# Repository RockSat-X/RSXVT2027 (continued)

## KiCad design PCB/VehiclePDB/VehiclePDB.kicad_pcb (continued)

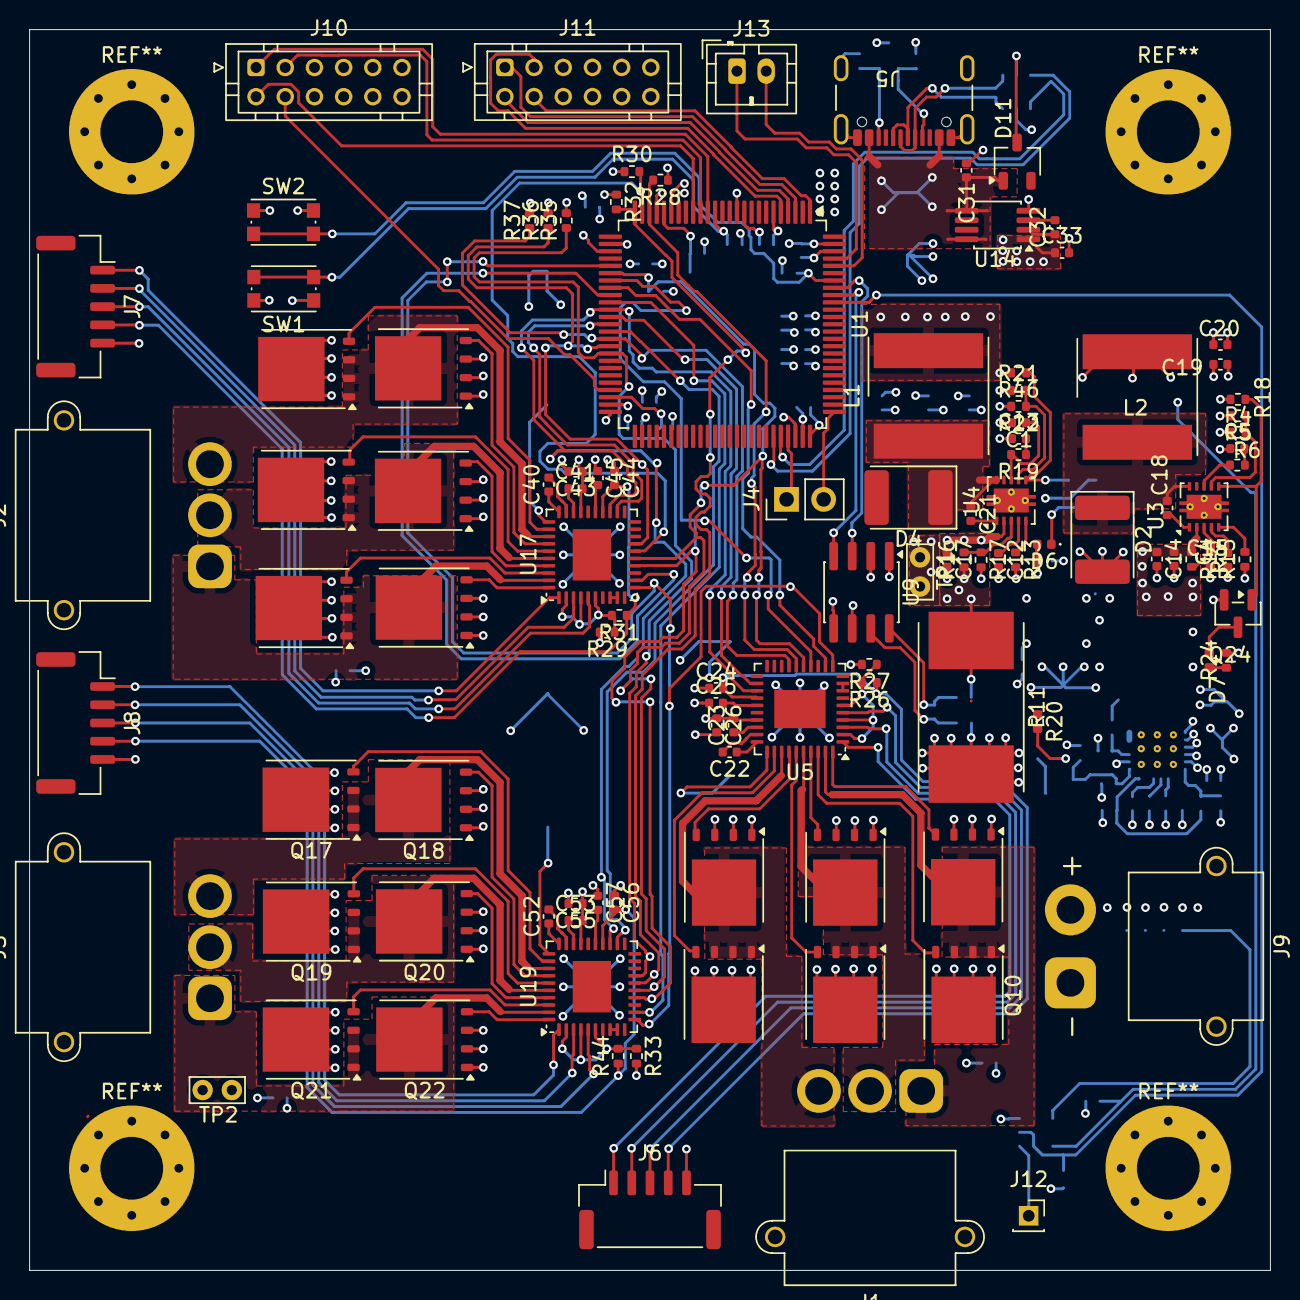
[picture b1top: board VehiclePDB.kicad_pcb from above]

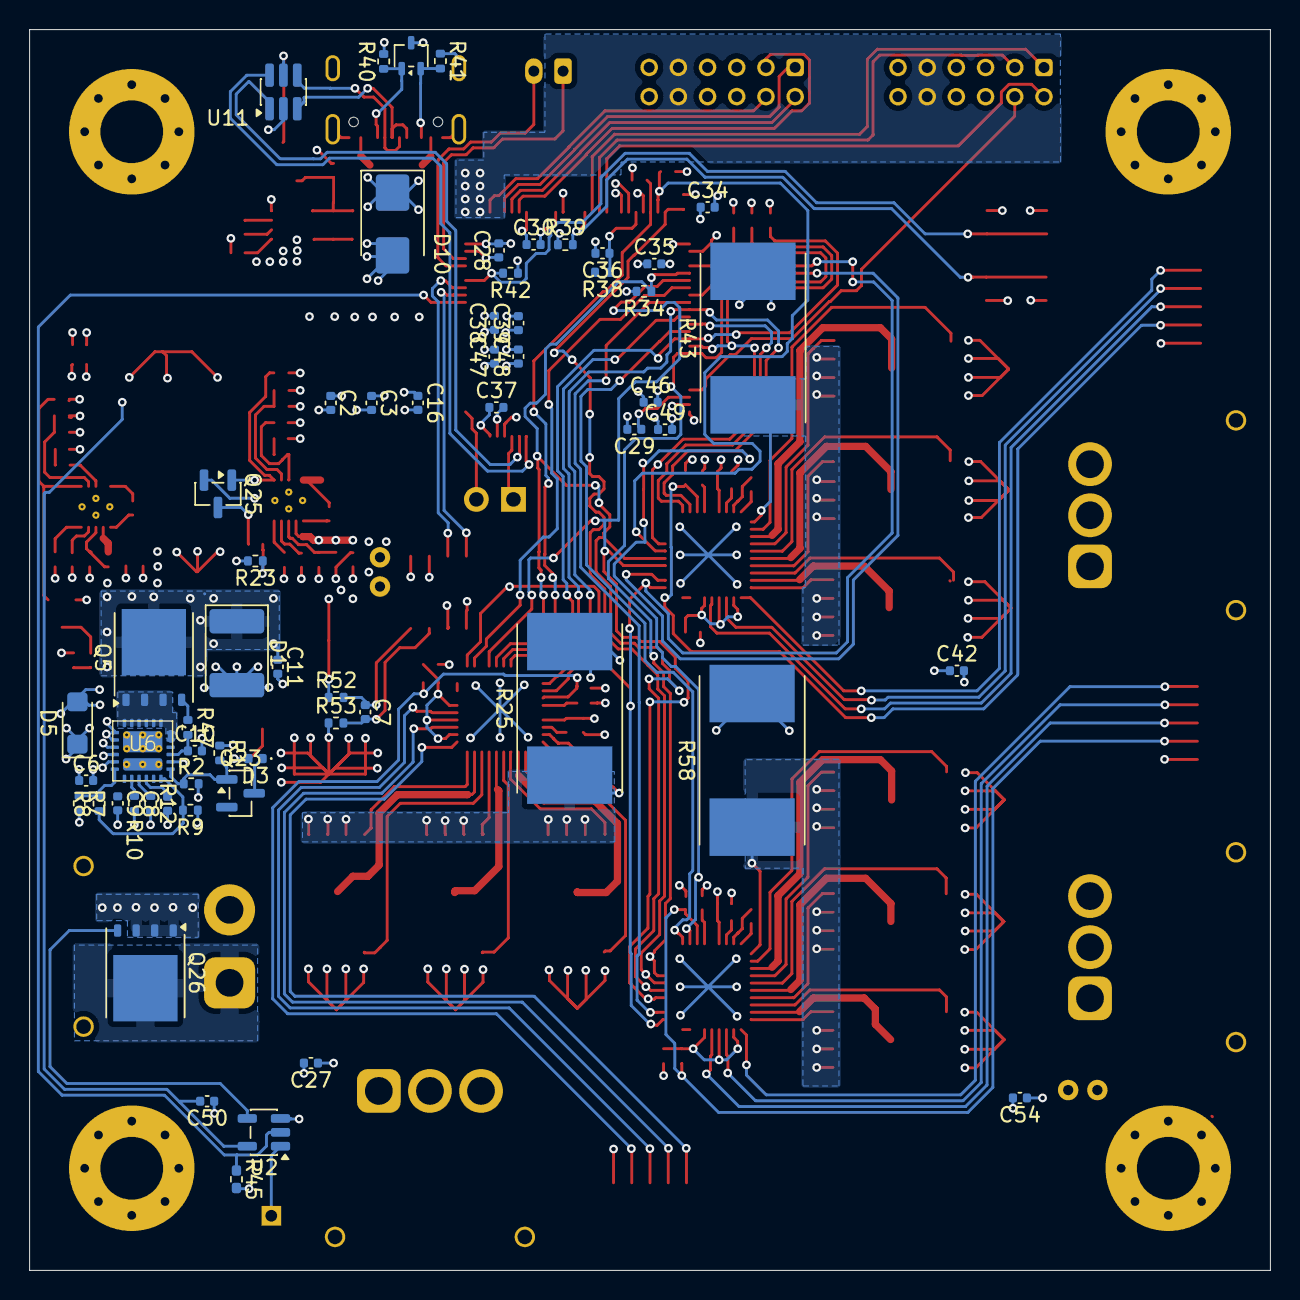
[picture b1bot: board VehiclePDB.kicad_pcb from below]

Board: 4 copper layers, 85.0 x 85.0 mm, 169 parts (59 on the bottom side), 150 nets.

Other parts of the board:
J7: Hall2; JST_GH_SM05B-GHS-TB_1x05-1MP_P1.25mm_Horizontal
Q11, Q12, Q13, Q14, Q15, Q16: BSC052N08NS5; TDSON-8-1
R29, R31: 4.7k; R_0402_1005Metric

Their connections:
/Motor Driver Two/Motors_Low: Q12.1 (S), Q12.2 (S), Q12.3 (S), Q14.1 (S), Q14.2 (S), Q14.3 (S), Q16.1 (S), Q16.2 (S), Q16.3 (S); also elsewhere on the board
/Motor Driver Two/U.High: Q11.4 (G); also elsewhere on the board
/Motor Driver Two/U.Low: Q12.4 (G); also elsewhere on the board
/Motor Driver Two/U.Switch: Q11.1 (S), Q11.2 (S), Q11.3 (S), Q12.5 (D); also elsewhere on the board
/Motor Driver Two/V.High: Q13.4 (G); also elsewhere on the board
/Motor Driver Two/V.Low: Q14.4 (G); also elsewhere on the board
/Motor Driver Two/V.Switch: Q13.1 (S), Q13.2 (S), Q13.3 (S), Q14.5 (D); also elsewhere on the board
/Motor Driver Two/W.High: Q15.4 (G); also elsewhere on the board
/Motor Driver Two/W.Low: Q16.4 (G); also elsewhere on the board
/Motor Driver Two/W.Switch: Q15.1 (S), Q15.2 (S), Q15.3 (S), Q16.5 (D); also elsewhere on the board
VMot: Q11.5 (D), Q13.5 (D), Q15.5 (D); also elsewhere on the board

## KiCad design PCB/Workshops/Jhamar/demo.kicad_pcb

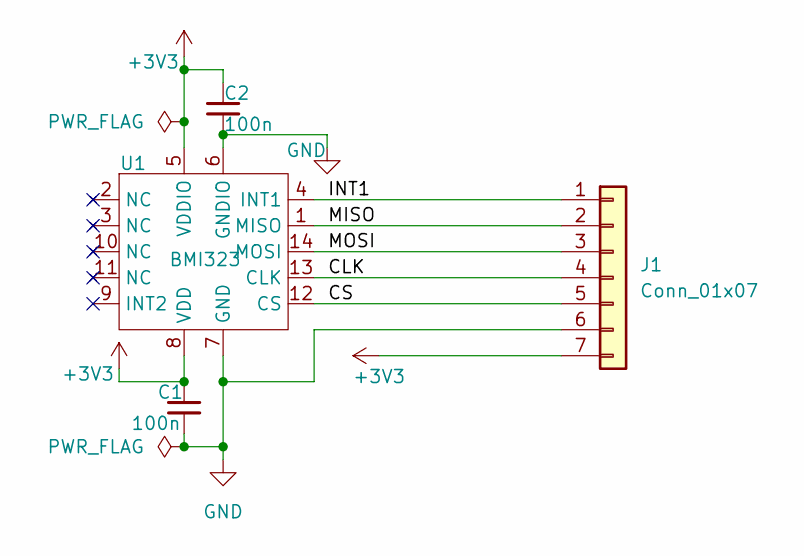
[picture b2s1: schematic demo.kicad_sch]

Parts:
C1, C2: 100n; C_0402_1005Metric
J1: Conn_01x07; PinSocket_1x07_P2.54mm_Vertical
U1: BMI323

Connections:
+3V3: C1.1, C2.1, J1.7, U1.5 (VDDIO), U1.8 (VDD)
/CLK: J1.4, U1.13 (CLK)
/CS: J1.5, U1.12 (CS)
/INT1: J1.1, U1.4 (INT1)
/MISO: J1.2, U1.1 (MISO)
/MOSI: J1.3, U1.14 (MOSI)
GND: C1.2, C2.2, J1.6, U1.6 (GNDIO), U1.7 (GND)

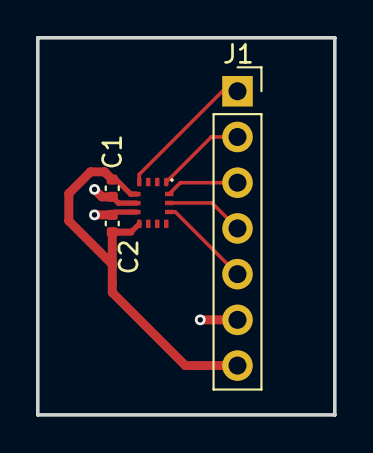
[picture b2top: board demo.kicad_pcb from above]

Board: 2 copper layers, 16.5 x 21.0 mm, 4 parts (0 on the bottom side), 7 nets.
